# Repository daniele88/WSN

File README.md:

# WSN

This is my Master thesis in Computer Engineering developed with Gianfranco Costamagna.
We developed an energy aware wireless sensors network. The PCB of the network nodes is designed with Eagle, and it is made up of: a MSP430, a battery meter, a RTC (optional) and a CC2500 antenna.
The firmware of the microcontroller was developed with CCStudio, an IDE provided by TI.
The project could be built and tested with a MSP430 LaunchPad kit, provided by TI.
The library to manage communication between MSP and CC2500 via SPI are from alvarop (https://github.com/alvarop/msp430-cc2500)
See master_thesis.pdf (in Italian language) for further details on the PCB of the nodes, on the architecture of the network, and the communication protocol (written and designed from scratch)

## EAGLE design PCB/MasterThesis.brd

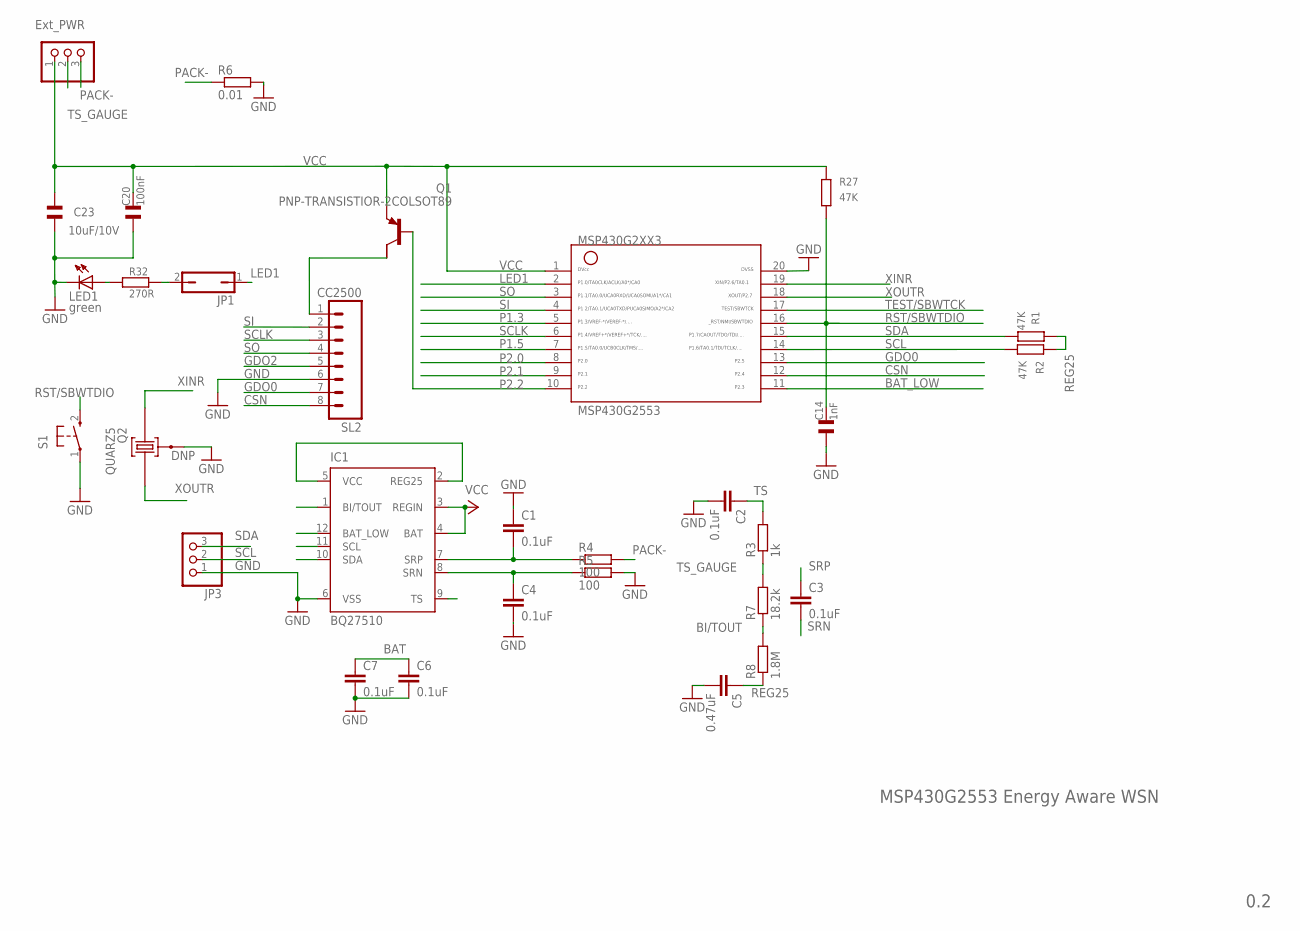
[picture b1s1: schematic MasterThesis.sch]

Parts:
C1, C2, C3, C4, C6, C7: 0.1uF; C025-024X044
C5: 0.47uF; C025-024X044
C14: 1nF; 0603
C20: 100nF; 0603
C23: 10uF/10V; 0805
IC1: BQ27510; DRZ; MPN BQ27510DRZT
J6: 1X03
JP1: JP1Q; JP1
JP3: PINHD-1X3/90; 1X03/90
LED1: green; DIODE0603
MSP430G2553: MSP430G2553; N20
Q1: PNP-TRANSISTIOR-2COLSOT89; SOT89
Q2: QUARZ5
R1, R2, R27: 47K; 0603
R3: 1k; 0204/5
R4, R5: 100; 0204/5
R6: 0.01; 0204/5
R7: 18.2k; 0204/5
R8: 1.8M; 0204/5
R32: 270R; 0603
S1: PB; PBTH
SL2: CC2500; 08P

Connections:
BAT: C6.1, C7.1, IC1.3 (REGIN), IC1.4 (BAT)
BAT_LOW: IC1.12 (BAT_LOW), MSP430G2553.11
BI/TOUT: IC1.1 (BI/TOUT), R7.1, R8.2
CSN: MSP430G2553.12, SL2.8
GDO0: MSP430G2553.13, SL2.7
GDO2: SL2.5
GND: C1.1, C2.2, C4.2, C5.2, C6.2, C7.2, C14.1, C20.1, C23.1, IC1.6 (VSS), JP3.1, LED1.K (C), MSP430G2553.20, Q2.GND@0 (0), R5.2, R6.2, S1.1, SL2.6
LED1: JP1.1, MSP430G2553.2
unnamed: Q1.2 (C), SL2.1
unnamed: JP1.2, R32.2
unnamed: LED1.A, R32.1
P1.3: MSP430G2553.5
P1.5: MSP430G2553.7
P2.0: MSP430G2553.8
P2.1: MSP430G2553.9
P2.2: MSP430G2553.10, Q1.1 (B)
PACK-: J6.3, R4.2, R6.1
PWPD: IC1.EXP@1 (PWPD), IC1.EXP@2 (PWPD), IC1.EXP@3 (PWPD), IC1.EXP@4 (PWPD), IC1.EXP@5 (PWPD), IC1.EXP@6 (PWPD), IC1.EXP@7 (PWPD), IC1.EXP@8 (PWPD), IC1.EXP@9 (PWPD)
REG25: C5.1, IC1.2 (REG25), IC1.5 (VCC), R1.1, R2.1, R8.1
RST/SBWTDIO: C14.2, MSP430G2553.16, R27.2, S1.2 (S)
SCL: IC1.11 (SCL), JP3.2, MSP430G2553.14, R2.2
SCLK: MSP430G2553.6, SL2.3
SDA: IC1.10 (SDA), JP3.3, MSP430G2553.15, R1.2
SI: MSP430G2553.4, SL2.2
SO: MSP430G2553.3, SL2.4
SRN: C3.2, C4.1, IC1.8 (SRN), R5.1
SRP: C1.2, C3.1, IC1.7 (SRP), R4.1
TEST/SBWTCK: MSP430G2553.17
TS: C2.1, IC1.9 (TS), R3.2
TS_GAUGE: J6.2, R3.1, R7.2
VCC: C20.2, C23.2, J6.1, MSP430G2553.1, Q1.3 (E), R27.1
XINR: MSP430G2553.19, Q2.2
XOUTR: MSP430G2553.18, Q2.1

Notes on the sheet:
MSP430G2553 Energy Aware WSN
Ext_PWR
DNP
0.2

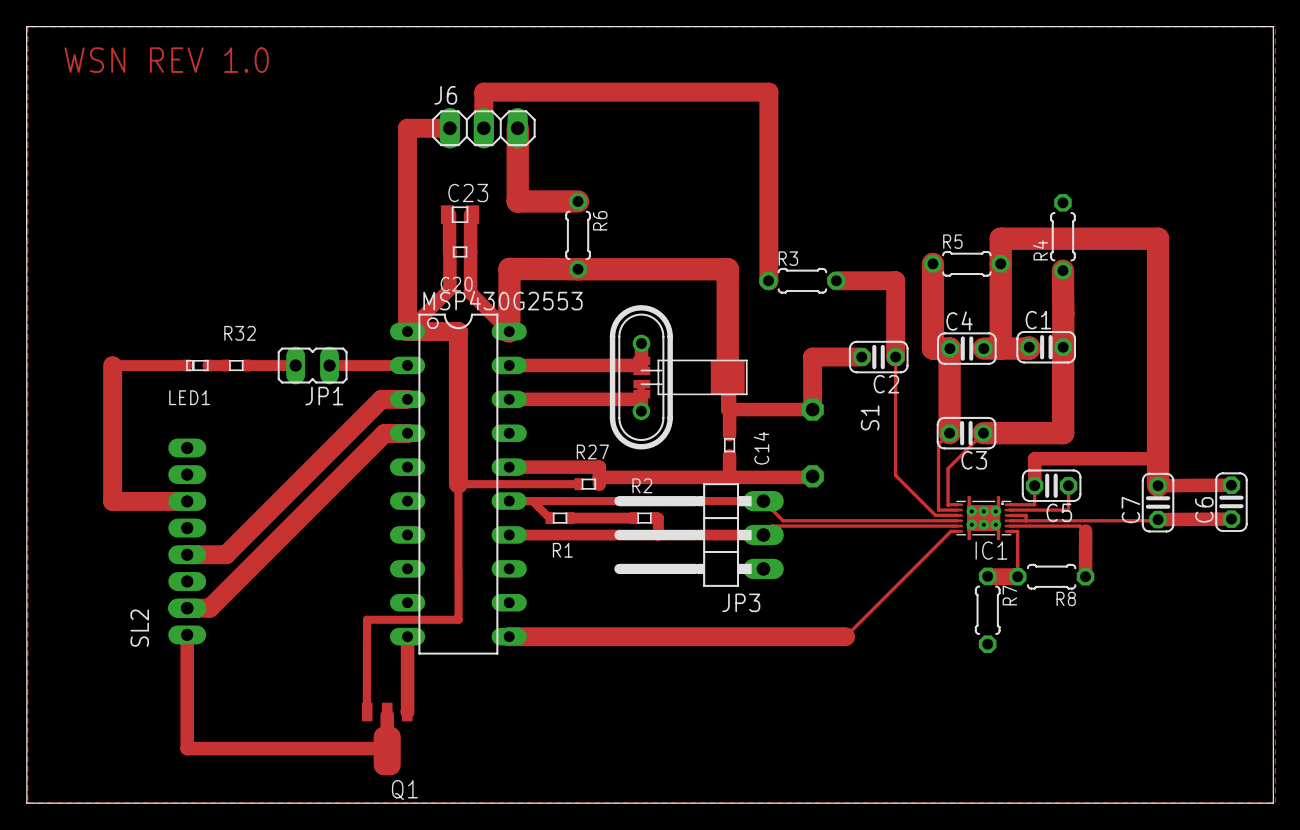
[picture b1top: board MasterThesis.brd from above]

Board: 2 copper layers, 93.4 x 58.2 mm, 30 parts (0 on the bottom side), 27 nets.

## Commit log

2015-01-29 modified readme
2015-01-29 minor modifications
2015-01-29 added thesis pdf
2015-01-29 added PCB
